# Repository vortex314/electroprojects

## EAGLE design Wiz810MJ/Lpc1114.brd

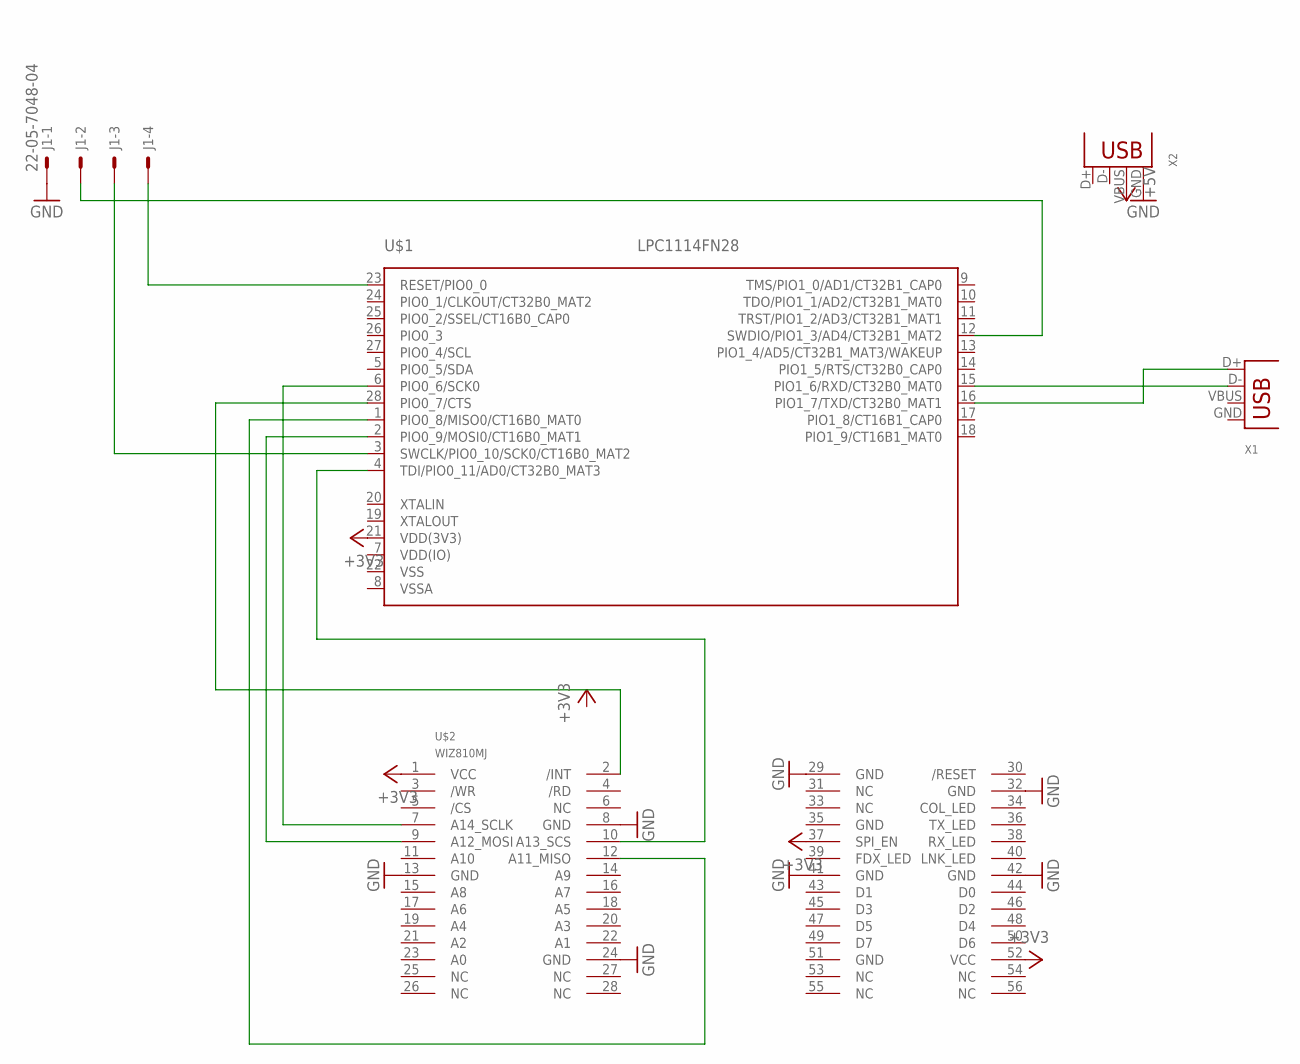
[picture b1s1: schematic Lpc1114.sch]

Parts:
J1: 22-05-7048-04; 7395-04
U$1: LPC1114FN28; DIP28
U$2: WIZ810MJ
X1: USB-A-H
X2: USB-B-H

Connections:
+3V3: U$1.21 (VDD(3V3)), U$2.1 (VCC), U$2.37 (SPI_EN), U$2.52 (VCC)
+5V: X2.VBUS
GND: J1.1, U$2.8 (GND), U$2.13 (GND), U$2.24 (GND), U$2.29 (GND), U$2.32 (GND), U$2.41 (GND), U$2.42 (GND), X2.GND
unnamed: U$1.6 (PIO0_6/SCK0), U$2.7 (A14_SCLK)
unnamed: U$1.2 (PIO0_9/MOSI0/CT16B0_MAT1), U$2.9 (A12_MOSI)
unnamed: U$1.1 (PIO0_8/MISO0/CT16B0_MAT0), U$2.12 (A11_MISO)
unnamed: J1.4, U$1.23 (RESET/PIO0_0)
unnamed: J1.3, U$1.3 (SWCLK/PIO0_10/SCK0/CT16B0_MAT2)
unnamed: J1.2, U$1.12 (SWDIO/PIO1_3/AD4/CT32B1_MAT2)
unnamed: U$1.16 (PIO1_7/TXD/CT32B0_MAT1), X1.D+
unnamed: U$1.15 (PIO1_6/RXD/CT32B0_MAT0), X1.D-
unnamed: U$1.4 (TDI/PIO0_11/AD0/CT32B0_MAT3), U$2.10 (A13_SCS)
unnamed: U$1.28 (PIO0_7/CTS), U$2.2 (/INT)
VDD(IO): U$1.7 (VDD(IO))
VSS: U$1.22 (VSS)
VSSA: U$1.8 (VSSA)

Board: 2 copper layers, 5 parts (0 on the bottom side), 12 nets, no tracks yet.
